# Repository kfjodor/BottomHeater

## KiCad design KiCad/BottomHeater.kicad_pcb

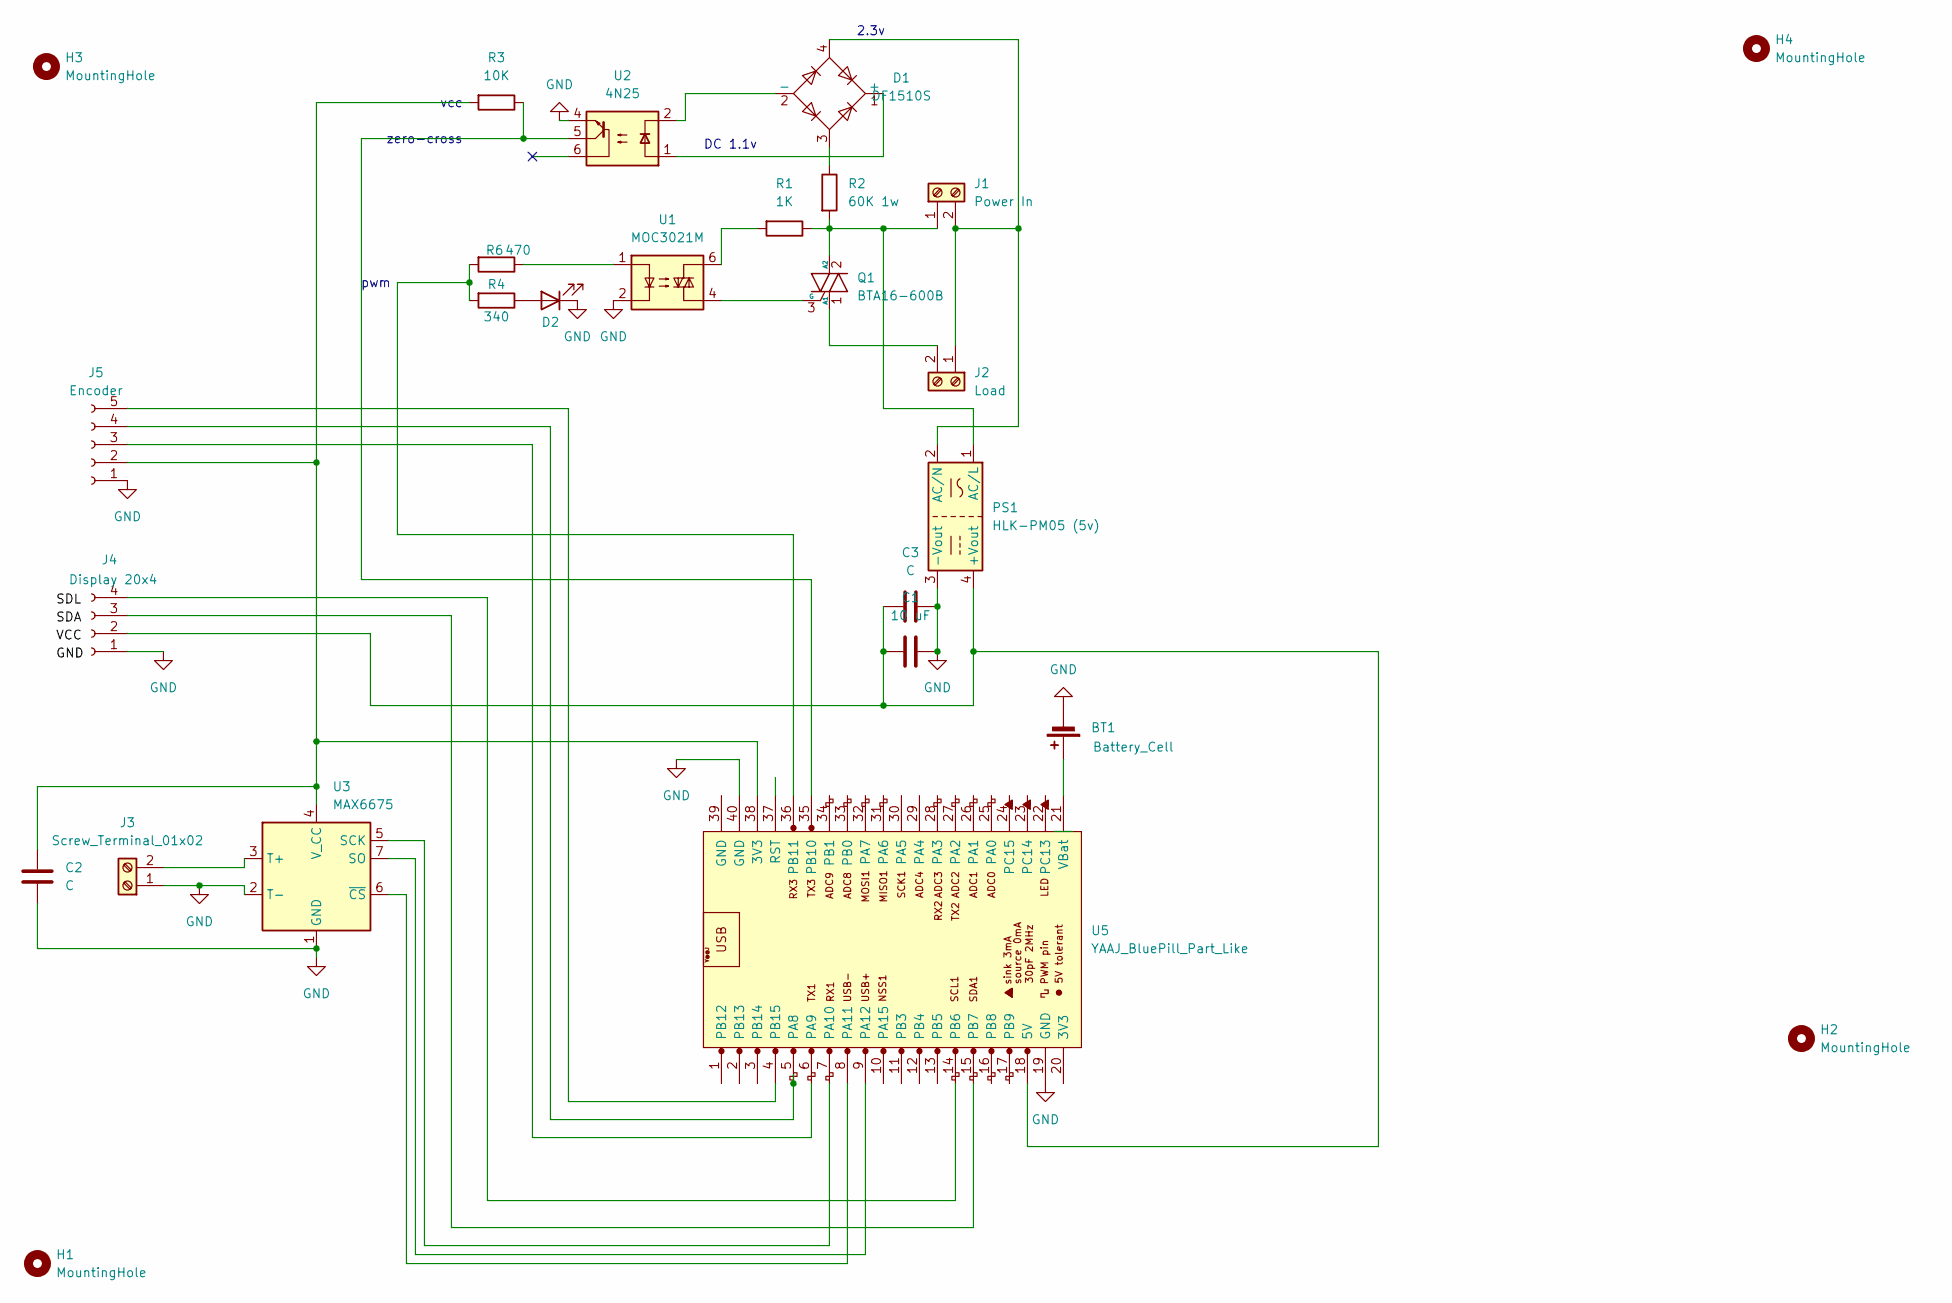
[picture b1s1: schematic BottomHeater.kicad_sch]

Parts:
BT1: Battery_Cell; Battery_Panasonic_CR2032-HFN_Horizontal_CircularHoles
C1: 10 uF; C_0603_1608Metric
C2: C; C_0603_1608Metric
C3: C; C_Radial_D5.0mm_H5.0mm_P2.00mm
D1: DF1510S; Diode_Bridge_OnSemi_SDIP-4L
D2: LED; LED_D3.0mm
H1, H2, H3, H4: MountingHole; MountingHole_2mm
J1: Power In; TerminalBlock_MaiXu_MX126-5.0-02P_1x02_P5.00mm
J2: Load; TerminalBlock_MaiXu_MX126-5.0-02P_1x02_P5.00mm
J3: Screw_Terminal_01x02; PhoenixContact_GMSTBVA_2,5_2-G-7,62_1x02_P7.62mm_Vertical
J4: Display 20x4; Molex_KK-254_AE-6410-05A_1x05_P2.54mm_Vertical
J5: Encoder; Molex_KK-254_AE-6410-05A_1x05_P2.54mm_Vertical
PS1: HLK-PM05 (5v); Converter_ACDC_Hi-Link_HLK-PMxx
Q1: BTA16-600B; TO-220-3_Vertical
R1: 1K; R_Axial_DIN0309_L9.0mm_D3.2mm_P15.24mm_Horizontal
R2: 60K 1w; R_Axial_DIN0309_L9.0mm_D3.2mm_P15.24mm_Horizontal
R3: 10K; R_1206_3216Metric
R4: 340; R_1206_3216Metric
R6: 470; R_1206_3216Metric
U1: MOC3021M; DIP-6_W7.62mm
U2: 4N25; DIP-6_W7.62mm
U3: MAX6675; SOIC-8_3.9x4.9mm_P1.27mm
U5: YAAJ_BluePill_Part_Like; YAAJ_BluePill_1

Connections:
GND: BT1.2 (-), C1.1, C2.2, C3.1, D2.1 (K), J3.1, J4.1, J5.1, PS1.3 (-Vout), U1.2, U2.4, U3.1 (GND), U3.2 (T-), U5.19 (GND), U5.40 (GND)
unnamed: BT1.1 (+), U5.21 (VBat)
unnamed: D1.1 (+), U2.1
unnamed: D1.2 (-), U2.2
unnamed: D1.3, R2.1
unnamed: D2.2 (A), R4.1
unnamed: J1.1, PS1.1 (AC/L), Q1.2 (A2), R1.1, R2.2
unnamed: D1.4, J1.2, J2.1, PS1.2 (AC/N)
unnamed: J2.2, Q1.1 (A1)
unnamed: J3.2, U3.3 (T+)
unnamed: C1.2, C3.2, J4.2, PS1.4 (+Vout), U5.18 (5V)
unnamed: J4.3, U5.15 (PB7)
unnamed: J4.4, U5.14 (PB6)
unnamed: C2.1, J5.2, R3.2, U3.4 (V_CC), U5.38 (3V3)
unnamed: J5.3, U5.6 (PA9)
unnamed: J5.4, U5.5 (PA8)
unnamed: J5.5, U5.4 (PB15)
unnamed: Q1.3 (G), U1.4
unnamed: R1.2, U1.6
unnamed: R6.1, U1.1
unnamed: U3.5 (SCK), U5.7 (PA10)
unnamed: U3.7 (SO), U5.9 (PA12)
unnamed: U3.6 (~CS), U5.8 (PA11)
unnamed: R3.1, U2.5, U5.35 (PB10)
unnamed: R4.2, R6.2, U5.36 (PB11)

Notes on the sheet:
pwm
DC 1.1v
vcc
2.3v
zero-cross

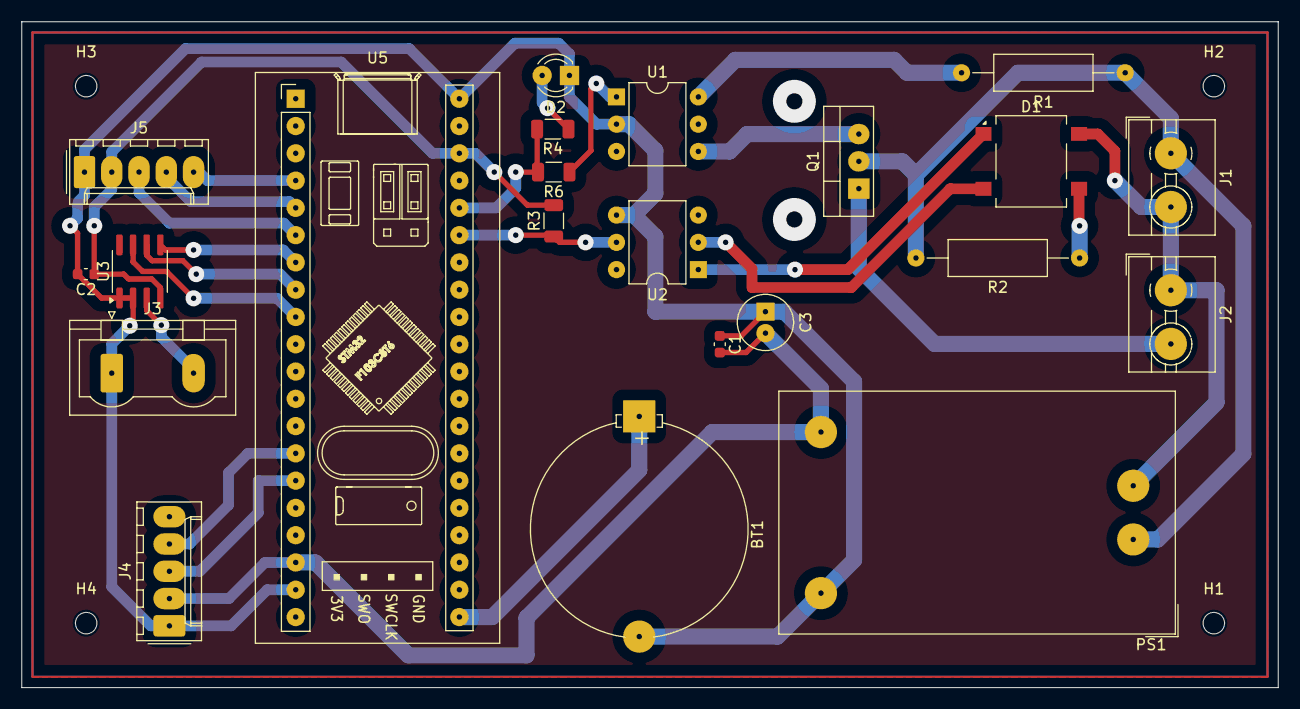
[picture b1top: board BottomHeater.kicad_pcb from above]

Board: 2 copper layers, 117.0 x 62.0 mm, 26 parts (0 on the bottom side), 25 nets.

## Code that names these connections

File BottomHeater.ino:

#include <HardwareTimer.h>
#include <Wire.h>
#include <LiquidCrystal_I2C.h>
#include <max6675.h>

#define MODE_TEMP 1
#define MODE_POWER 2

#define MAXCLK PA10
#define MAXCS PA11
#define MAXDO PA12

#define ENCODER_S1 PB15  //PB13
#define ENCODER_S2 PA8   //PB14
#define ENCODER_KEY PA9  //PB15

#define TRIAC_ZERO_CROSS PB10
#define TRIAC_PWM PB11

MAX6675 thermocouple(MAXCLK, MAXCS, MAXDO);
LiquidCrystal_I2C lcd(0x27, 16, 2);  // set the LCD address to 0x27 for a 16 chars and 2 line display
HardwareTimer outTimer(TIM3);

int mode = MODE_TEMP;
float temp = 0;
float prevTemp = 0;
float prevTemp3sec = 0;
unsigned long prevMillis = 0;

int count = 0;
float heat_eff = 0;
int desiredTemp = 0;
bool tempChanged = false;
volatile int power = 20;  // 0 - 100
bool powerChanged = false;
int powerDelay = 0;  // 1-9999 for 50Hz
const int measurementCycles = 3;
unsigned long prevRotation = 0;

void setup() {
  lcd.init();
  lcd.init();
  lcd.backlight();

  desiredTemp = thermocouple.readCelsius();

  pinMode(ENCODER_S1, INPUT_PULLUP);
  pinMode(ENCODER_S2, INPUT_PULLUP);
  pinMode(ENCODER_KEY, INPUT_PULLUP);
  pinMode(TRIAC_ZERO_CROSS, INPUT);
  pinMode(TRIAC_PWM, OUTPUT);

  // Button pressed on start
  if (digitalRead(ENCODER_KEY) == LOW) {
    mode = MODE_POWER;
  }

  attachInterrupt(digitalPinToInterrupt(TRIAC_ZERO_CROSS), ZeroCross, RISING);
  attachInterrupt(digitalPinToInterrupt(ENCODER_S1), EncoderRotate, FALLING);
  //attachInterrupt(digitalPinToInterrupt(ENCODER_KEY), EncoderKey, FALLING);

  printPower(power, heat_eff);
}

void printTemp(float temp1, int temp2) {
  lcd.setCursor(0, 0);
  lcd.print("                ");
  lcd.setCursor(0, 0);
  if (mode == MODE_TEMP) {
    lcd.print("*");
  }
  lcd.print(temp1);

  if (int(temp1) == temp2) {
    lcd.print(" == ");
  } else {
    lcd.print(" -> ");
  }

  lcd.print(temp2);
}

void printPower(int power, float heat_eff) {
  lcd.setCursor(0, 1);
  lcd.print("                ");
  lcd.setCursor(0, 1);
  if (mode == MODE_POWER) {
    lcd.print("*");
  }
  lcd.print("P:" + String(power) + "% ");
  lcd.print("E:" + String(heat_eff, 1));
}

void timerTriac() {
  digitalWrite(TRIAC_PWM, HIGH);
}

void ZeroCross() {
  digitalWrite(TRIAC_PWM, LOW);

  outTimer.pause();
  outTimer.attachInterrupt(timerTriac);
  outTimer.setOverflow(powerDelay, MICROSEC_FORMAT);
  outTimer.refresh();
  outTimer.resume();
}

void EncoderRotate() {
  if (mode == MODE_TEMP) {
    EncoderRotateTemp();
  } else {
    EncoderRotatePower();
  }
}

void EncoderKey() {
  if (mode == MODE_TEMP) {
    EncoderKeyTemp();
  } else {
    EncoderKeyPower();
  }
}

void EncoderRotateTemp() {
  unsigned long changeValue = 1;
  unsigned long currentRotation = micros();

  if (currentRotation - prevRotation < 10000) {
    changeValue = 20;
  } else if (currentRotation - prevRotation < 20000) {
    changeValue = 10;
  }

  prevRotation = currentRotation;

  if (digitalRead(ENCODER_S1) == LOW && digitalRead(ENCODER_S2) == LOW) {
    desiredTemp += changeValue;
  } else if (digitalRead(ENCODER_S1) == LOW && digitalRead(ENCODER_S2) == HIGH) {
    desiredTemp -= changeValue;
  }

  if (desiredTemp < 0) {
    desiredTemp = 0;
  }

  tempChanged = true;
}

void EncoderKeyTemp() {
  desiredTemp += 10;
  tempChanged = true;
}

void EncoderRotatePower() {
  if (digitalRead(ENCODER_S2) == LOW) {
    power++;
  } else {
    power--;
  }

  // noInterrupts failed on stm32 on main loop so checking here
  if (power > 100) {
    power = 100;
  } else if (power < 0) {
    power = 0;
  } else {
    powerChanged = true;
  }
}

void EncoderKeyPower() {
  power += 10;

  // noInterrupts failed on stm32 on main loop so checking here
  if (power > 100) {
    power = 100;
  } else if (power < 0) {
    power = 0;
  }

  powerChanged = true;
}

void setPowerDelay(int power) {
  powerDelay = (100 - power) * 100;
}

void loopPower() {
  unsigned long nowMillis = millis();

  if (prevMillis + 1000 < nowMillis) {
    temp = thermocouple.readCelsius();
    if (temp != prevTemp) {
      tempChanged = true;
      prevTemp = temp;
      printTemp(temp, 0);
    }

    prevMillis = nowMillis;
    count++;

    // 3 секундный счетчик
    if (count == measurementCycles) {
      heat_eff = temp - prevTemp3sec;  // скорость нагрева в 3 секунд
      prevTemp3sec = temp;
      count = 0;
      printPower(power, heat_eff);
    }
  }

  if (powerChanged) {
    setPowerDelay(power);
    printPower(power, heat_eff);
    powerChanged = false;
  }
}

float heat_eff_min;
float heat_eff_max;

void loopTemp() {
  unsigned long nowMillis = millis();

  // каждые 1 сек обновляем температуру
  if (prevMillis + 1000 < nowMillis) {
    temp = thermocouple.readCelsius();
    if (temp != prevTemp) {
      tempChanged = true;
      prevTemp = temp;
    }

    prevMillis = nowMillis;

    count++;

    // 3 sec loop
    if (count == measurementCycles) {
      count = 0;
      heat_eff = temp - prevTemp3sec;
      prevTemp3sec = temp;

      // нагрев
      if (desiredTemp > temp) {
        float diff = desiredTemp - temp;
        if (diff > 50) {
          power = diff / 2;
        } else {
          heat_eff_min = diff / 15;
          heat_eff_max = diff / 10;

          if (heat_eff < heat_eff_min) {
            power++;
          }
          if (heat_eff > heat_eff_max) {
            power--;
          }
        }
      } else if (desiredTemp < temp) {  // охлаждение
        if (heat_eff > 0) {
          power--;
        }
      } else {  // Required temp acquired
        if (heat_eff > 0.5) {
          power--;
        } else if (heat_eff < 0.5) {
          power++;
        }
      }

      if (power > 100) {
        power = 100;
      } else if (power < 0) {
        power = 0;
      }

      setPowerDelay(power);
      printPower(power, heat_eff);
    }  // measurementCycles
  }    // 1 sec loop

  // покрутили ручку или произошел нагрев
  if (tempChanged) {
    printTemp(temp, desiredTemp);
    tempChanged = false;
  }
}

void loop() {
  if (mode == MODE_TEMP) {
    loopTemp();
  } else if (mode = MODE_POWER) {
    loopPower();
  }
}

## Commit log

2024-09-24 work in progress
2024-12-04 board almost done
2024-12-10 source
2024-12-19 heating algorithm experiment
2025-01-05 remove symlink
2025-01-05 add KiCad project
2025-01-11 not linear rotation speed
